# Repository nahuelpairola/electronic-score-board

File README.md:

# score-board
## Score Board circuit and program, using Arduino and LED strips. It is working, and really well :)

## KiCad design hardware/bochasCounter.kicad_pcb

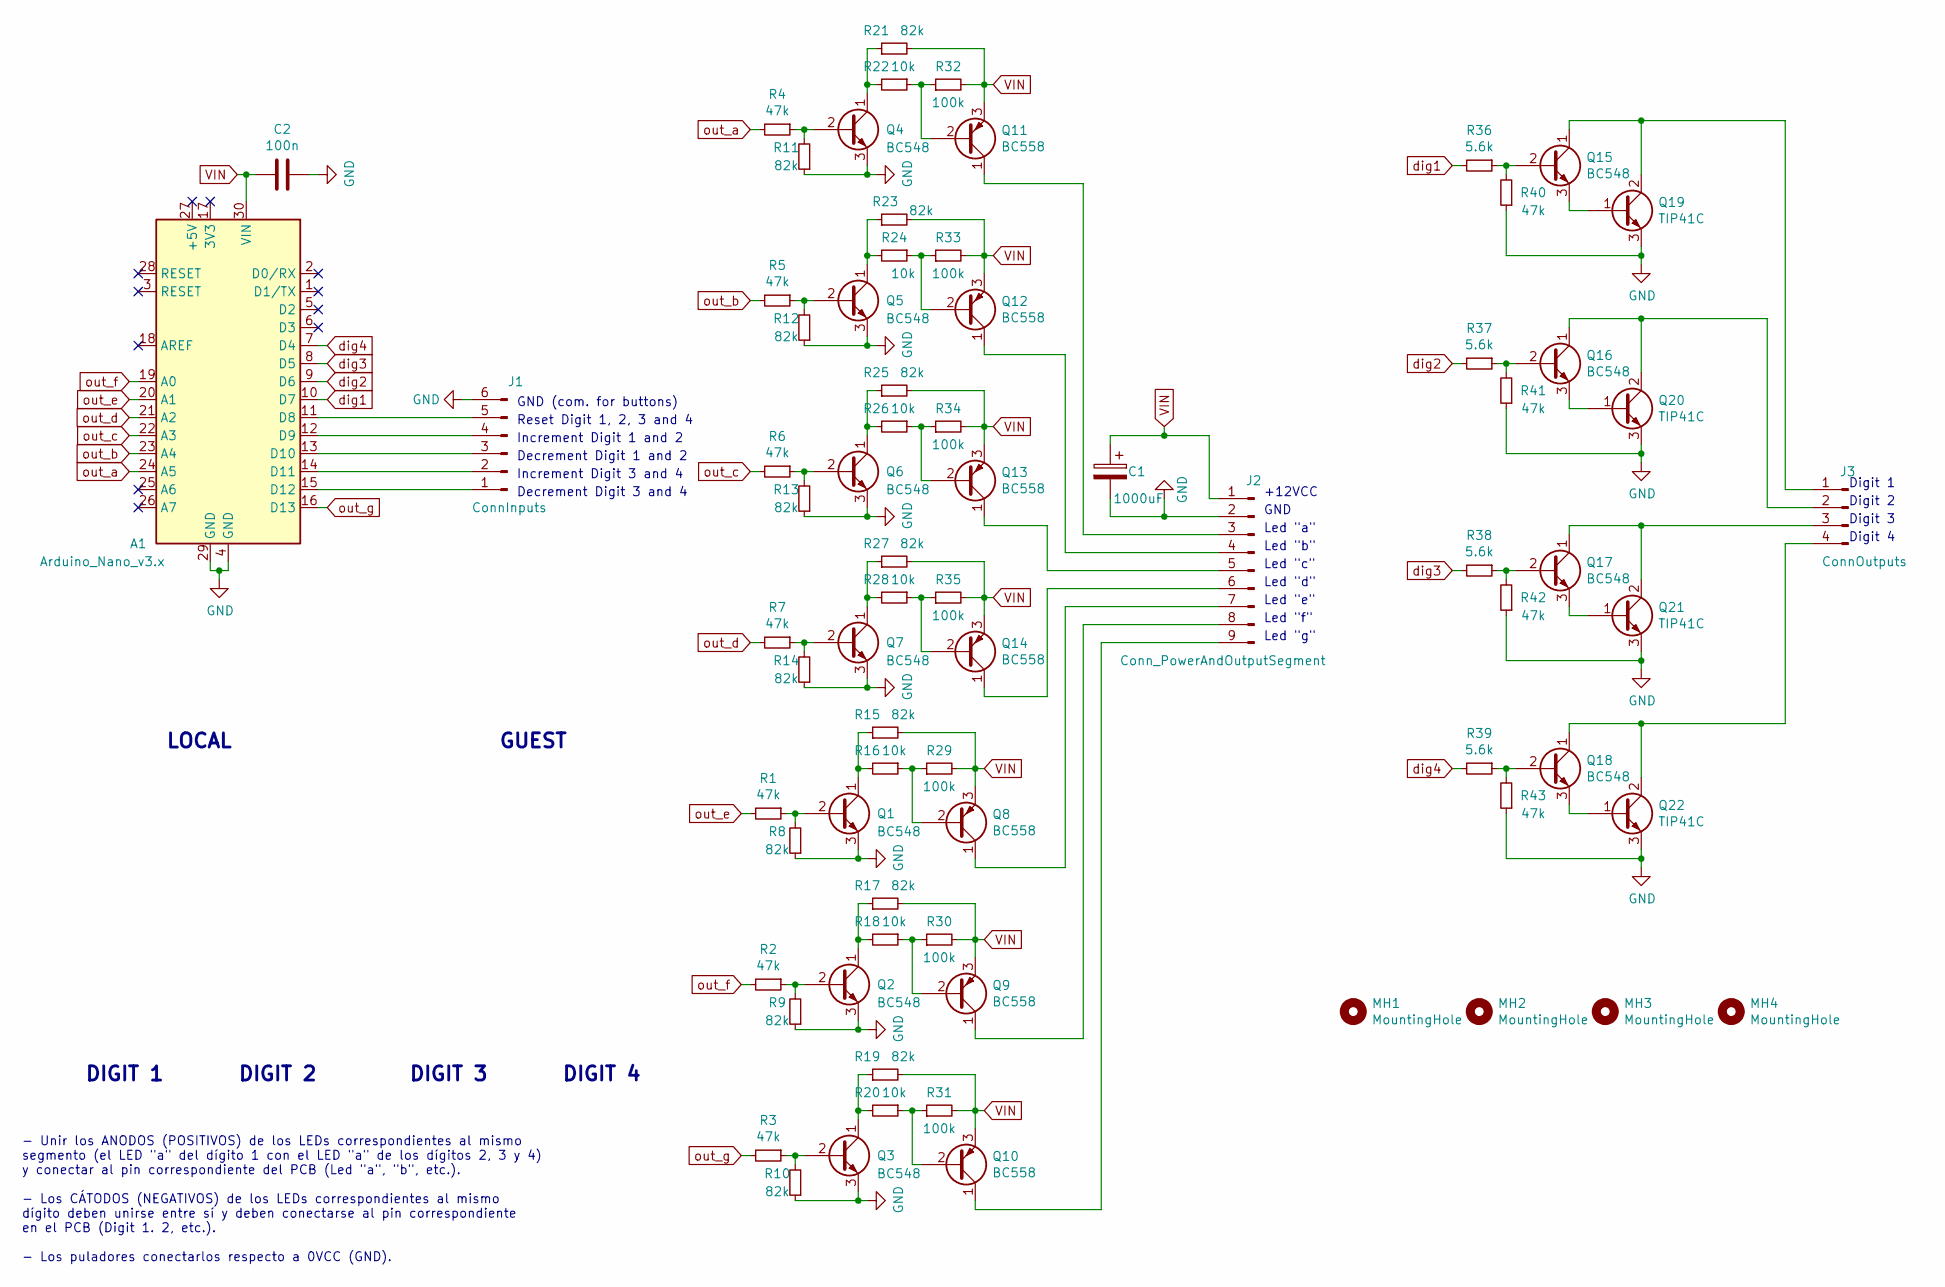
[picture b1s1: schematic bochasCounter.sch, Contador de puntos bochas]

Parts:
A1: Arduino_Nano_v3.x; Arduino_Nano_WithMountingHoles
C1: 1000uF; CP_Radial_D12.5mm_P5.00mm
C2: 100n; C_Disc_D3.0mm_W2.0mm_P2.50mm
J1: ConnInputs; PinHeader_1x06_P2.54mm_Horizontal
J2: Conn_PowerAndOutputSegment; PinHeader_1x09_P2.54mm_Horizontal
J3: ConnOutputs; PinHeader_1x04_P2.54mm_Horizontal
MH1, MH2, MH3, MH4: MountingHole; Fiducial_Modern_CopperBottom
Q1, Q2, Q3, Q4, Q5, Q6, Q7: BC548; TO-92L_Inline_Wide
Q8, Q9, Q10, Q11, Q12, Q13, Q14: BC558; TO-92L_Inline_Wide
Q15, Q16, Q17, Q18: BC548; TO-92L_HandSolder
Q19, Q20, Q21, Q22: TIP41C; TO-220-3_Vertical
R1, R2, R3, R4, R5, R6, R7, R40, R41, R42, R43: 47k; R_Axial_DIN0204_L3.6mm_D1.6mm_P5.08mm_Horizontal
R8, R9, R10, R11, R12, R13, R14, R15, R17, R19, R21, R23, R25, R27: 82k; R_Axial_DIN0204_L3.6mm_D1.6mm_P5.08mm_Horizontal
R16, R18, R20, R22, R24, R26, R28: 10k; R_Axial_DIN0204_L3.6mm_D1.6mm_P5.08mm_Horizontal
R29, R30, R31, R32, R33, R34, R35: 100k; R_Axial_DIN0204_L3.6mm_D1.6mm_P5.08mm_Horizontal
R36, R37, R38, R39: 5.6k; R_Axial_DIN0204_L3.6mm_D1.6mm_P5.08mm_Horizontal

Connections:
GND: A1.4 (GND), A1.29 (GND), C1.2, C2.1, J1.6, J2.2, Q1.3 (E), Q2.3 (E), Q3.3 (E), Q4.3 (E), Q5.3 (E), Q6.3 (E), Q7.3 (E), Q19.3 (E), Q20.3 (E), Q21.3 (E), Q22.3 (E), R8.1, R9.1, R10.1, R11.1, R12.1, R13.1, R14.1, R40.1, R41.1, R42.1, R43.1
unnamed: A1.11 (D8), J1.5
unnamed: A1.12 (D9), J1.4
unnamed: A1.13 (D10), J1.3
unnamed: A1.14 (D11), J1.2
unnamed: A1.15 (D12), J1.1
unnamed: J2.3, Q11.1 (C)
unnamed: J2.4, Q12.1 (C)
unnamed: J2.5, Q13.1 (C)
unnamed: J2.6, Q14.1 (C)
unnamed: J2.7, Q8.1 (C)
unnamed: J2.8, Q9.1 (C)
unnamed: J2.9, Q10.1 (C)
unnamed: J3.1, Q15.1 (C), Q19.2 (C)
unnamed: J3.2, Q16.1 (C), Q20.2 (C)
unnamed: J3.3, Q17.1 (C), Q21.2 (C)
unnamed: J3.4, Q18.1 (C), Q22.2 (C)
unnamed: Q1.1 (C), R15.1, R16.2
unnamed: Q1.2 (B), R1.1, R8.2
unnamed: Q2.1 (C), R17.1, R18.2
unnamed: Q2.2 (B), R2.1, R9.2
unnamed: Q3.1 (C), R19.1, R20.2
unnamed: Q3.2 (B), R3.1, R10.2
unnamed: Q4.1 (C), R21.1, R22.2
unnamed: Q4.2 (B), R4.1, R11.2
unnamed: Q5.1 (C), R23.1, R24.2
unnamed: Q5.2 (B), R5.1, R12.2
unnamed: Q6.1 (C), R25.1, R26.2
unnamed: Q6.2 (B), R6.1, R13.2
unnamed: Q7.1 (C), R27.1, R28.2
unnamed: Q7.2 (B), R7.1, R14.2
unnamed: Q8.2 (B), R16.1, R29.1
unnamed: Q9.2 (B), R18.1, R30.1
unnamed: Q10.2 (B), R20.1, R31.1
unnamed: Q11.2 (B), R22.1, R32.1
unnamed: Q12.2 (B), R24.1, R33.1
unnamed: Q13.2 (B), R26.1, R34.1
unnamed: Q14.2 (B), R28.1, R35.1
unnamed: Q15.2 (B), R36.1, R40.2
unnamed: Q15.3 (E), Q19.1 (B)
unnamed: Q16.2 (B), R37.1, R41.2
unnamed: Q16.3 (E), Q20.1 (B)
unnamed: Q17.2 (B), R38.1, R42.2
unnamed: Q17.3 (E), Q21.1 (B)
unnamed: Q18.2 (B), R39.1, R43.2
unnamed: Q18.3 (E), Q22.1 (B)
VIN: A1.30 (VIN), C1.1, C2.2, J2.1, Q8.3 (E), Q9.3 (E), Q10.3 (E), Q11.3 (E), Q12.3 (E), Q13.3 (E), Q14.3 (E), R15.2, R17.2, R19.2, R21.2, R23.2, R25.2, R27.2, R29.2, R30.2, R31.2, R32.2, R33.2, R34.2, R35.2
dig1: A1.10 (D7), R36.2
dig2: A1.9 (D6), R37.2
dig3: A1.8 (D5), R38.2
dig4: A1.7 (D4), R39.2
out_a: A1.24 (A5), R4.2
out_b: A1.23 (A4), R5.2
out_c: A1.22 (A3), R6.2
out_d: A1.21 (A2), R7.2
out_e: A1.20 (A1), R1.2
out_f: A1.19 (A0), R2.2
out_g: A1.16 (D13), R3.2

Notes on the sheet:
GND
+12VCC
Led "a"
Led "b"
Led "c"
Led "d"
Led "e"
Led "f"
Led "g"
Digit 1
Digit 2
Digit 3
Digit 4
Decrement Digit 3 and 4
GND (com. for buttons)
Increment Digit 3 and 4
Increment Digit 1 and 2
Decrement Digit 1 and 2
Reset Digit 1, 2, 3 and 4
DIGIT 1
DIGIT 2
DIGIT 3
DIGIT 4
- Unir los ANODOS (POSITIVOS) de los LEDs correspondientes al mismo segmento (el LED "a" del dígito 1 con el LED "a" de los dígitos 2, 3 y 4) y conectar al pin correspondiente del PCB (Led "a", "b", etc.). - Los CÁTODOS (NEGATIVOS) de los LEDs correspondientes al mismo dígito deben unirse entre sí 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
LOCAL
GUEST

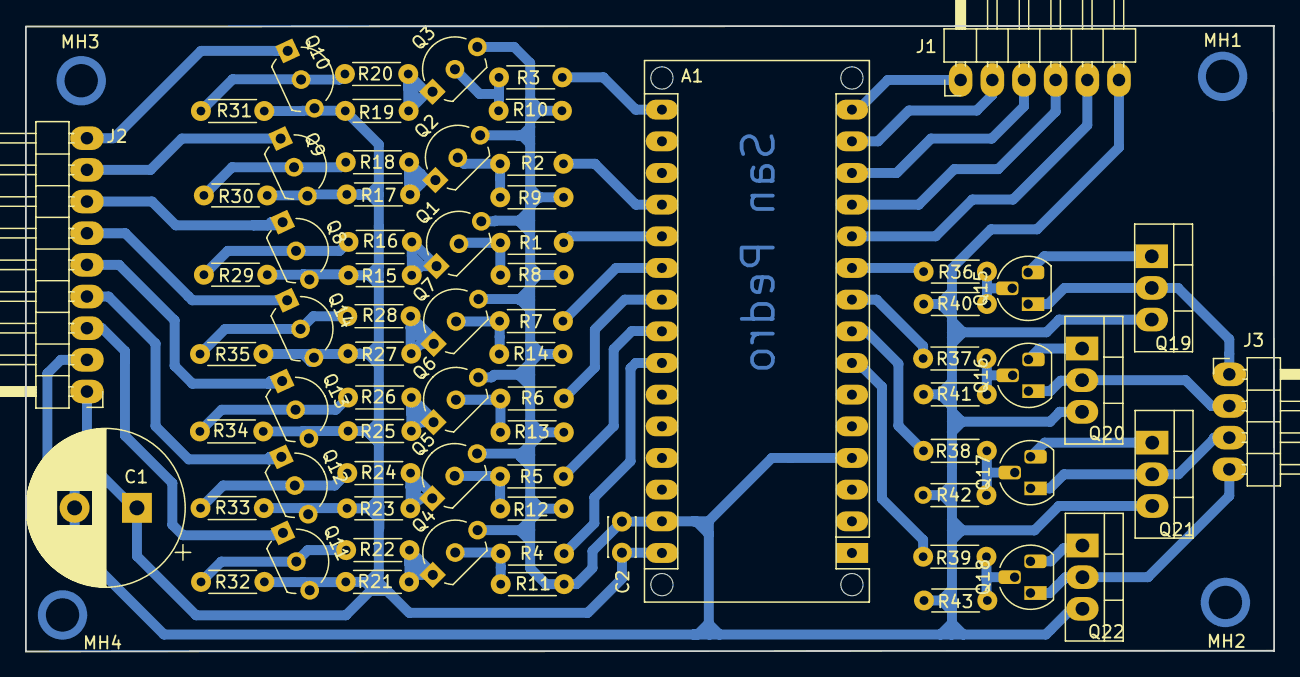
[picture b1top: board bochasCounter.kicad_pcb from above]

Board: 2 copper layers, 100.1 x 50.2 mm, 75 parts (0 on the bottom side), 58 nets.

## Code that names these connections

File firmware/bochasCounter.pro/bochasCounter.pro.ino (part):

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
// define outputs
// define pins to code
#define out_a A5
#define out_b A4    
#define out_c A3   
#define out_d A2   
#define out_e A1   
#define out_f A0  
#define out_g 13

#define dig1 PD7   // When digital out=1, enables digit 1
#define dig2 PD6   
#define dig3 PD5   
#define dig4 PD4   

// define inputs
#define pinReset          8    // D8 reset pin
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// Functions
void configuration(void) {
  // IO config
  pinMode(out_a, OUTPUT);
  pinMode(out_b, OUTPUT);
  pinMode(out_c, OUTPUT);
  pinMode(out_d, OUTPUT);
  pinMode(out_e, OUTPUT);
  pinMode(out_f, OUTPUT);
  pinMode(out_g, OUTPUT);
  pinMode(dig1, OUTPUT);
  pinMode(dig2, OUTPUT);
  pinMode(dig3, OUTPUT);
  pinMode(dig4, OUTPUT);
  pinMode(pinReset, INPUT_PULLUP);
  pinMode(pinIncrementHome, INPUT_PULLUP);
  pinMode(pinDecrementHome, INPUT_PULLUP);
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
